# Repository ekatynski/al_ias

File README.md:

View this project on [CADLAB.io](https://cadlab.io/project/28763). 

# al_ias
A PC boot switch, inspired largely by the [PokeyPow prototype](https://www.ajfriesen.com/my-first-electronic-hardware-pc) by Andrej Friesen.

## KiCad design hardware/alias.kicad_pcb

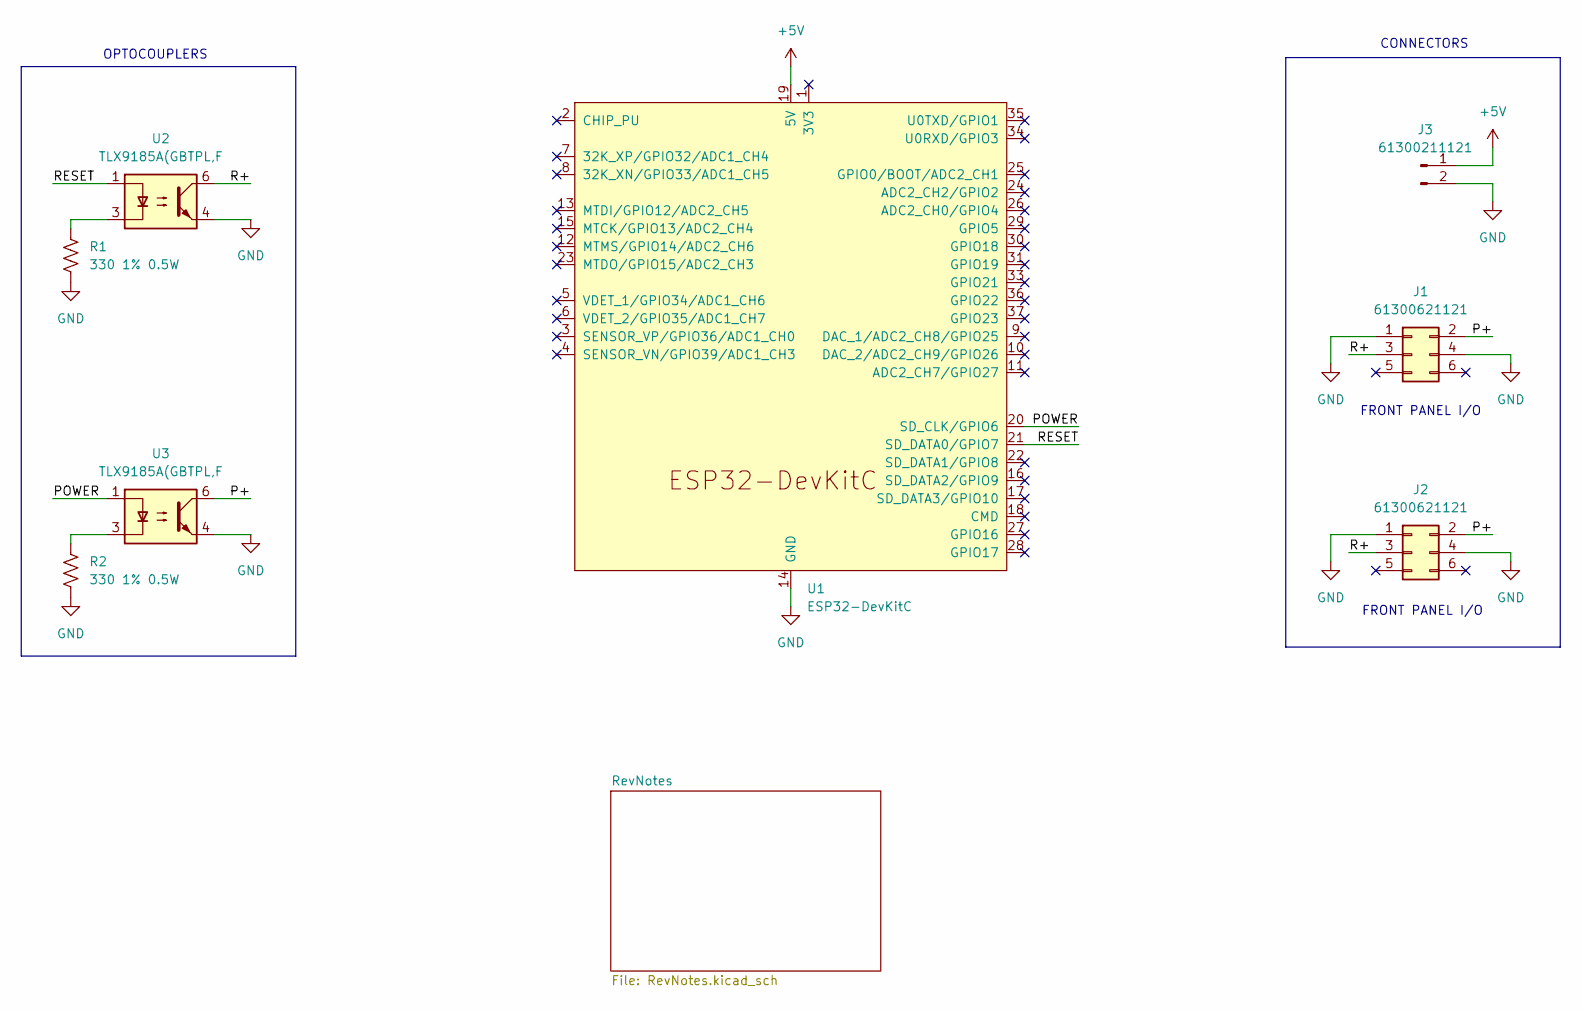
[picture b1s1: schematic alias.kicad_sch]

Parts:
J1, J2: 61300621121; PinHeader_2x03_P2.54mm_Vertical
J3: 61300211121; PinHeader_1x02_P2.54mm_Vertical
R1, R2: 330 1% 0.5W; R_0805_2012Metric_Pad1.20x1.40mm_HandSolder
U1: ESP32-DevKitC
U2, U3: TLX9185A(GBTPL,F; SO-6_4.4x3.6mm_P1.27mm

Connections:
+5V: J3.1, U1.19 (5V)
/P+: J1.2, J2.2, U3.6
/POWER: U1.20 (SD_CLK/GPIO6), U3.1
/R+: J1.3, J2.3, U2.6
/RESET: U1.21 (SD_DATA0/GPIO7), U2.1
GND: J1.1, J1.4, J2.1, J2.4, J3.2, R1.2, R2.2, U1.14 (GND), U1.32 (GND), U1.38 (GND), U2.4, U3.4
unnamed: R1.1, U2.3
unnamed: R2.1, U3.3

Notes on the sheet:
CONNECTORS
OPTOCOUPLERS
FRONT PANEL I/O

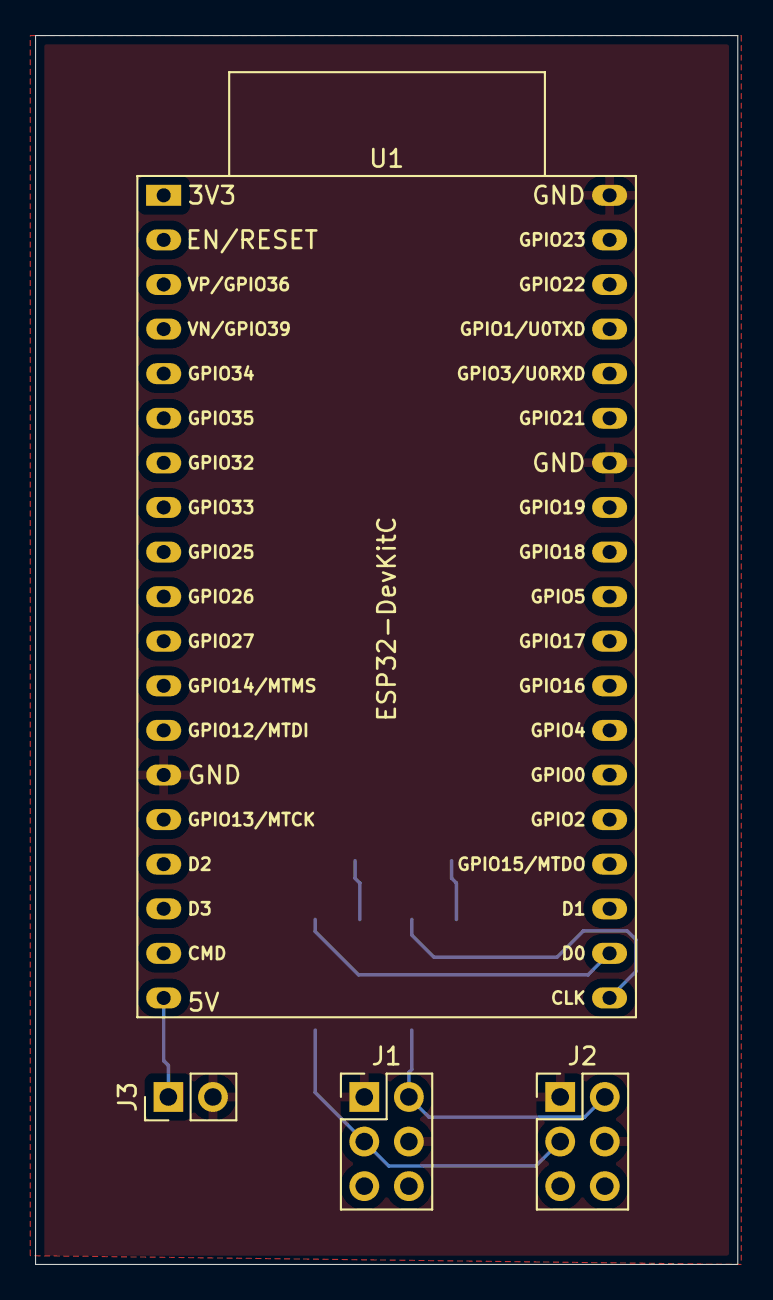
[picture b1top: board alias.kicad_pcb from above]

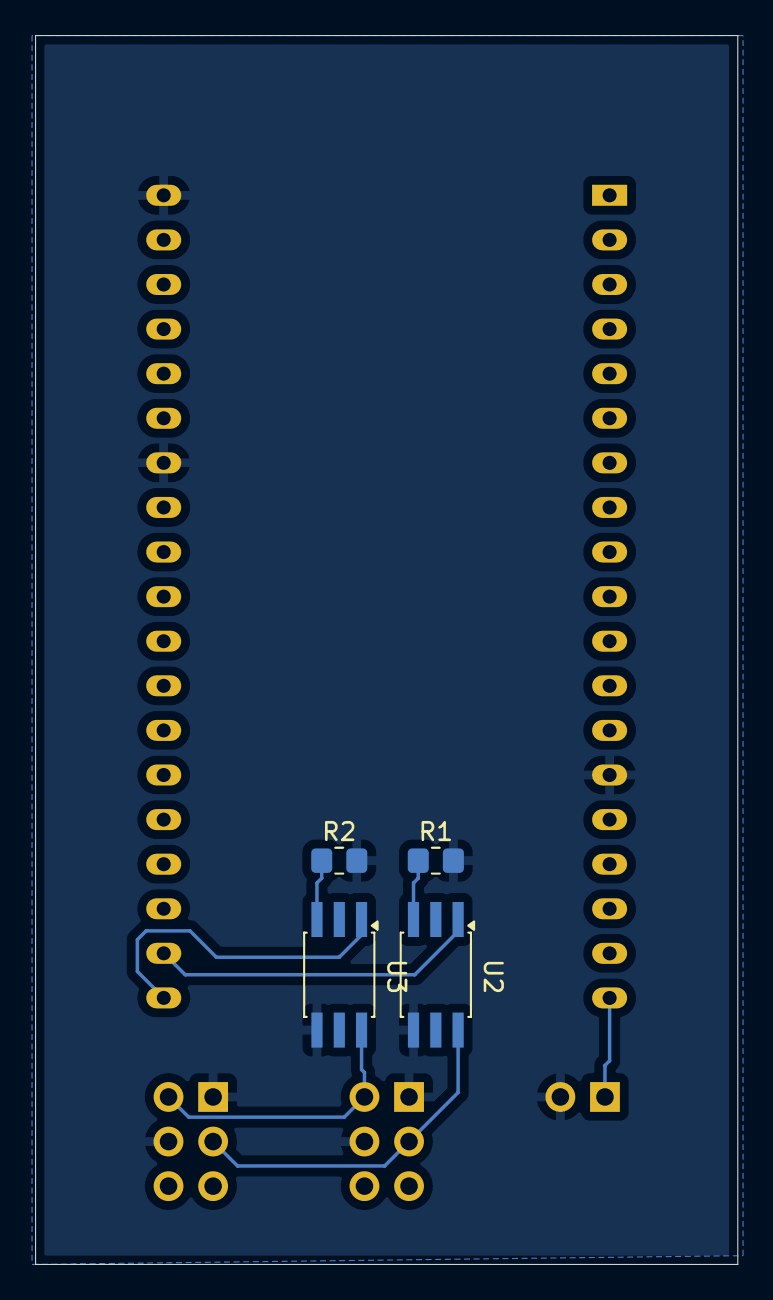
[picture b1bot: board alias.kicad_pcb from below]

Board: 2 copper layers, 40.0 x 70.0 mm, 8 parts (4 on the bottom side), 8 nets.

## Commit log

2024-12-31 Backlink to CADLAB.io has been added.
2024-12-31 Initialized project files, updated readme, added .gitignore.
2024-12-31 Updated README.
2025-01-02 Initial revision.
